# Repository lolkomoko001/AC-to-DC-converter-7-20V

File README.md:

<h1>Hello</h1> I made Small (5x3,5cm) AC to DC converter for 7 V-20 V . Withou heatsink for tranzistor its usable to around 10 V or 200mA before heating much . I made it at school with acid so its sort of double layer one for components and the other for traces. It took me around 1,5 hours to fully complete it. If you have any recommendations how to make it better type :)

---------------------------------------------------------------------------------------------------------------------------------------------------------------------------------------------------------------------------------
Components are mirrored like i have on my board 
items used:

4x wires

4x 1N4007 diodes

1x LED diode

1x capacitor 100uF

1x capacitor 0,1uF

1x 470ohm resistor

1x tranzistor L7805CP 

and one 5x3,5 cm pcb
---------------------------------------------------------------------------------------------------------------------------------------------------------------------------------------------------------------------------------
Here are some photos of the project

(The acid ate some of the copper so thats why it looks like that)

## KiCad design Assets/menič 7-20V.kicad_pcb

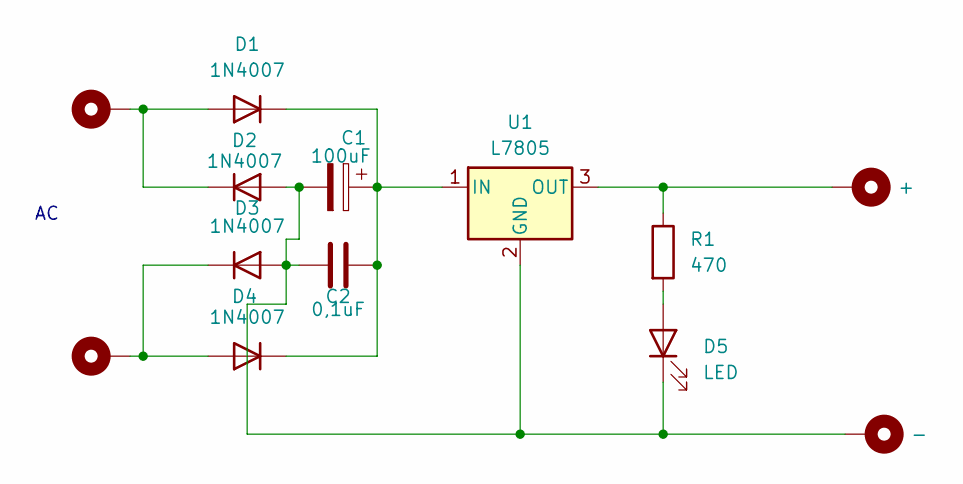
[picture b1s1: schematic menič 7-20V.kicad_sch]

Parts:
C1: 100uF; CP_Radial_D5.0mm_P2.50mm
C2: 0,1uF; C_Disc_D3.4mm_W2.1mm_P2.50mm
D1, D2, D3, D4: 1N4007; D_DO-41_SOD81_P10.16mm_Horizontal
D5: LED; LED_D5.0mm
H1, H2: MountingHole_Pad; MountingHole_2.2mm_M2_DIN965_Pad
H5: +; MountingHole_2.2mm_M2_DIN965_Pad
H6: -; MountingHole_2.2mm_M2_DIN965_Pad
R1: 470; R_Axial_DIN0204_L3.6mm_D1.6mm_P7.62mm_Horizontal
U1: L7805; TO-220F-3_Vertical

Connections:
unnamed: D1.2 (A), D2.1 (K), H1.1
unnamed: C1.1, C2.2, D1.1 (K), D4.1 (K), U1.1 (IN)
unnamed: C1.2, C2.1, D2.2 (A), D3.2 (A), D5.1 (K), H6.1, U1.2 (GND)
unnamed: D3.1 (K), D4.2 (A), H2.1
unnamed: D5.2 (A), R1.2
unnamed: H5.1, R1.1, U1.3 (OUT)

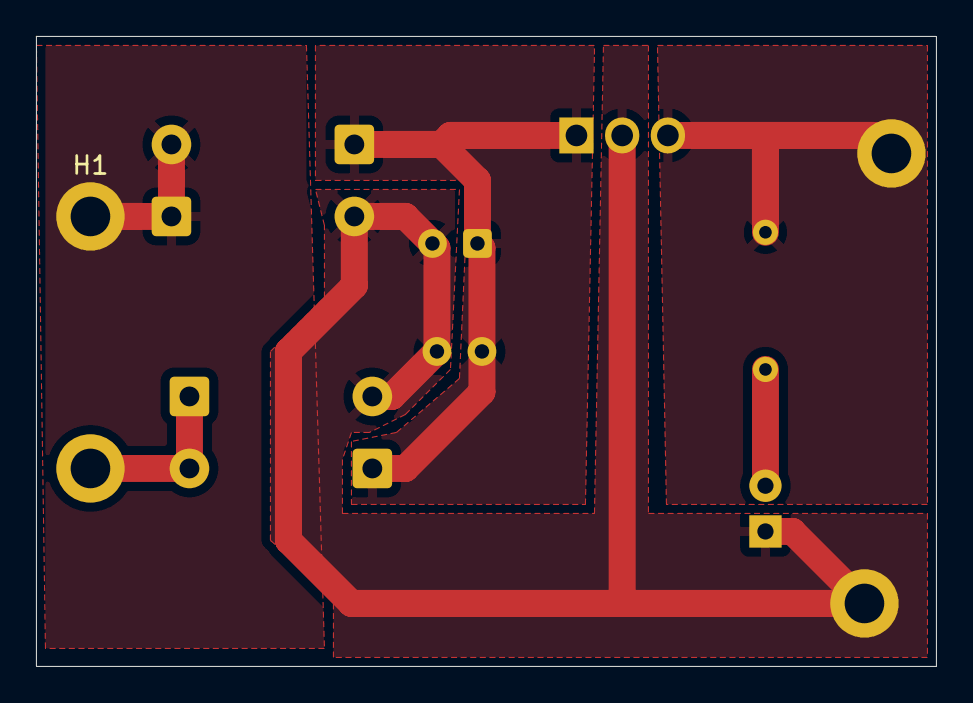
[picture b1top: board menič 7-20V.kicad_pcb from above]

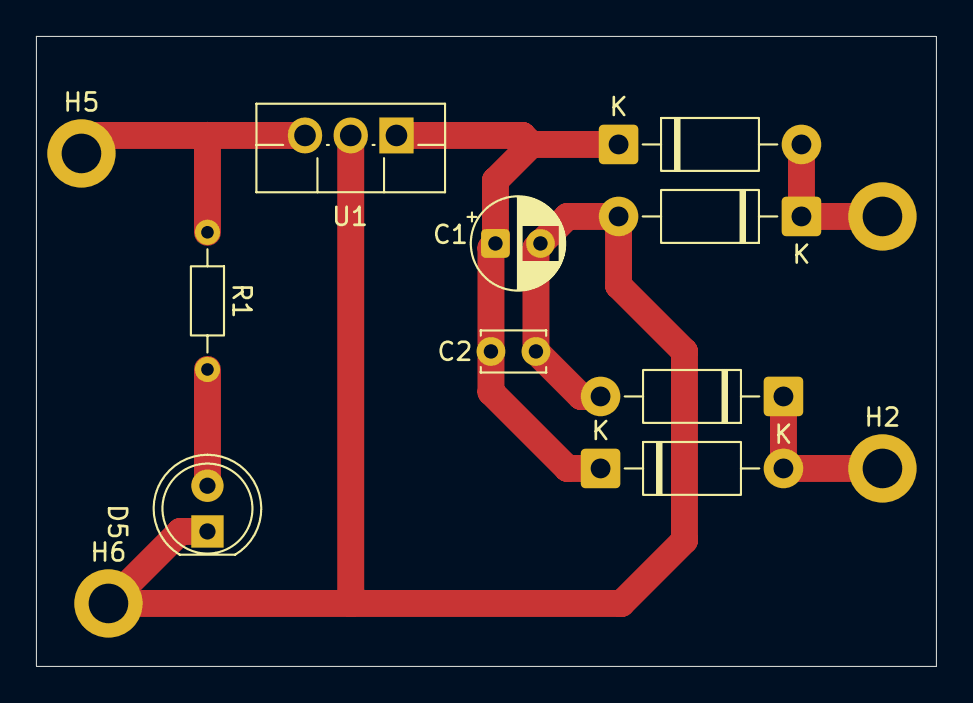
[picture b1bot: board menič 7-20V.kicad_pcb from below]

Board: 2 copper layers, 50.0 x 35.0 mm, 13 parts (12 on the bottom side), 6 nets.

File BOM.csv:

Product name ,QTY,Designator,Cost {retail} ,link 
4x wires,4,,?,
4x 1N4007 diodes,4,D1  D2 D3 D4,"0.16  (0,04  per unit)",https://www.drotik-elektro.sk/arduino-platforma/1076-usmerno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
"1x LED diode
",1,D5,"0,03 ",https://techfun.sk/produkt/led-ka-1-kus-5mm-rozne-farby/?att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
"1x capacitor 100uF
",1,C1,"0,05  ",https://www.elecom.sk/el-100uf-35v-2/
"1x capacitor 0,1uF
",1,C2,0.28 ,https://www.sparkfun.com/capacitor-ceramic-0-1uf.html
"1x 470ohm resistor
",1,R1,"0,02 ",https://techfun.sk/produkt/rezistor-rozne-hodnoty-1-4w-10-ku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
"1x tranzistor L7805CP
",1,U1,"0,85 ",https://www.tme.eu/sk/details/l7805cp/stabilizatory-napatia-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
" 5x3,5 cm pcb
",1,,?,

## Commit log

2025-12-11 Update README.md
    Replaced old images with new screenshots in README.
2025-12-11 Create Assets
2025-12-11 Create f
2025-12-11 Update README.md
    Updated the README with project details and components used.
2025-12-11 Create 1
2025-12-12 Update README with more project images and note
    Added additional images to the project section and included a note about the condition of the copper.
